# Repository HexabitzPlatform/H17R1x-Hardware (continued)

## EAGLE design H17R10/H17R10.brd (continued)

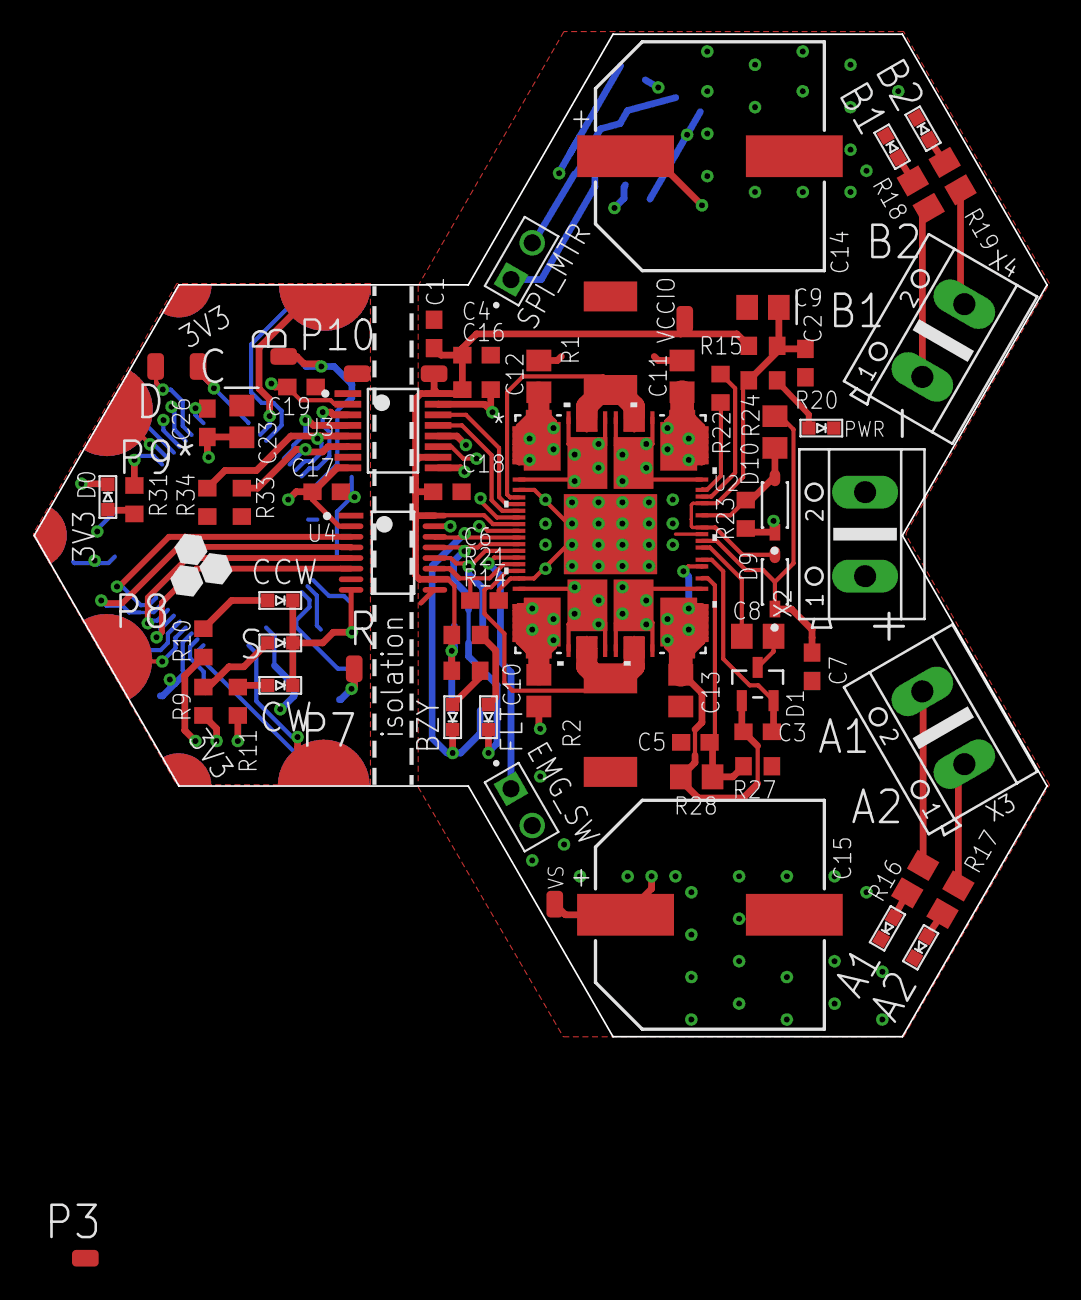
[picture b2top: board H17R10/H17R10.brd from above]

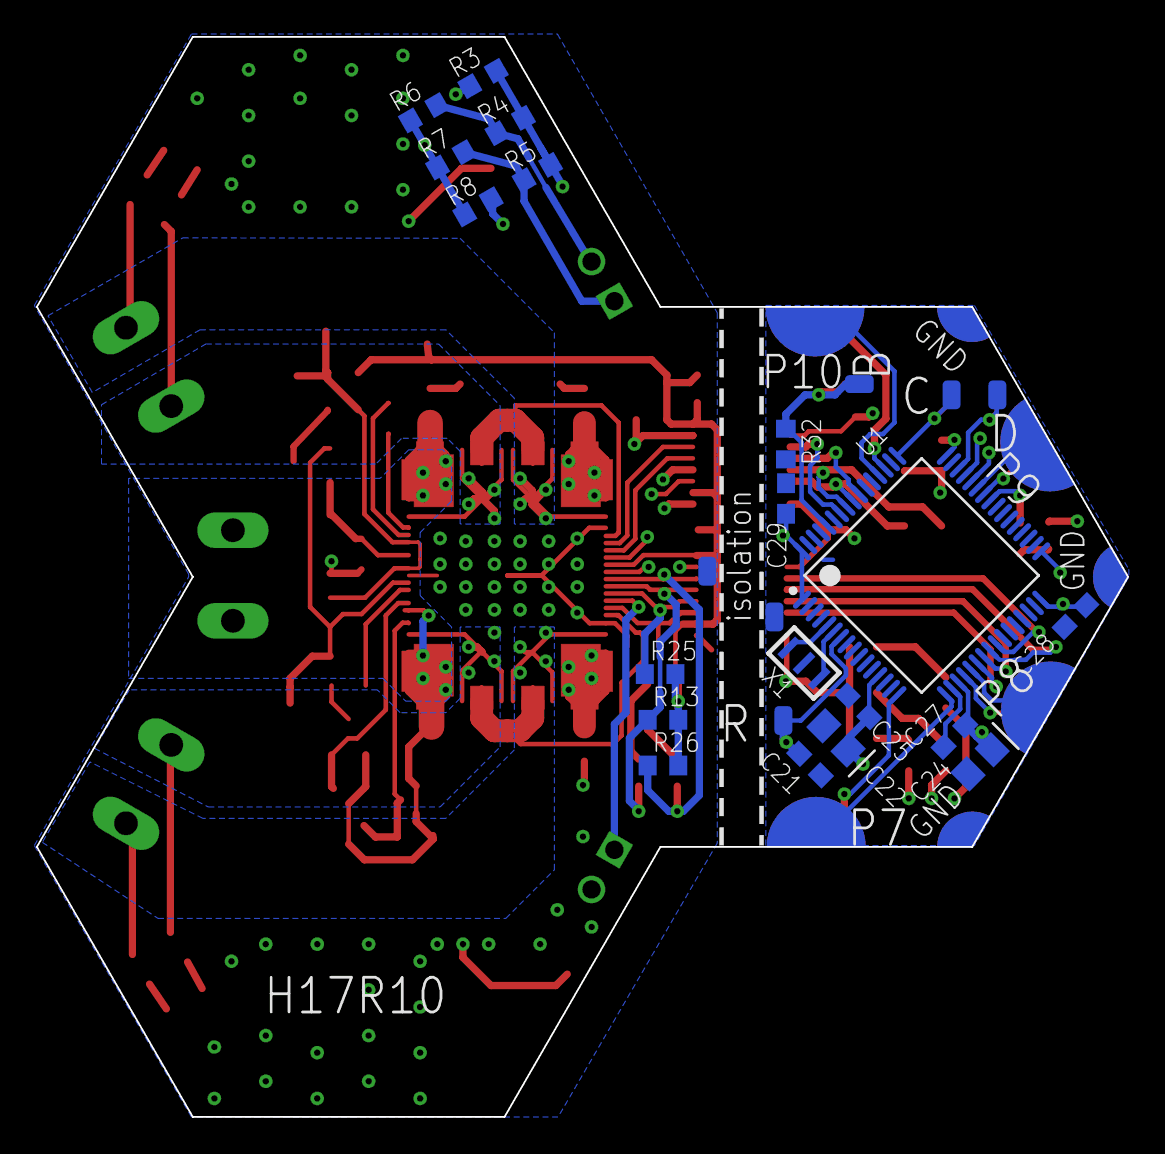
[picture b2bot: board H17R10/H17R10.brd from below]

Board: 4 copper layers, 60.6 x 60.0 mm, 95 parts (21 on the bottom side), 70 nets.

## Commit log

2021-03-25 finished schematics refrenced by ST module & adding isolation
2021-03-25 R24 added
2021-04-03 finished board >>> unchecked
2021-04-16 no message
2021-04-19 final with output files
2021-04-19 with documentation
2021-04-22 - Updated BOM..
2022-11-28 -Changing the MCU to STM32G0B1CEU6N -Editing the electronic design -Editing the layout design to improve the performance
2022-11-29 -Adding some components to the design to improve the performance
2022-11-29 -Editing in the layout design
2022-12-28 -Replace the blind vias with through hole ones
2023-02-15 -Correcting some documentation issues
2023-09-16 -Connect missing wires - Delete power led - Improve the layout for better performance and appearance
2023-09-16 -Edit readme file
